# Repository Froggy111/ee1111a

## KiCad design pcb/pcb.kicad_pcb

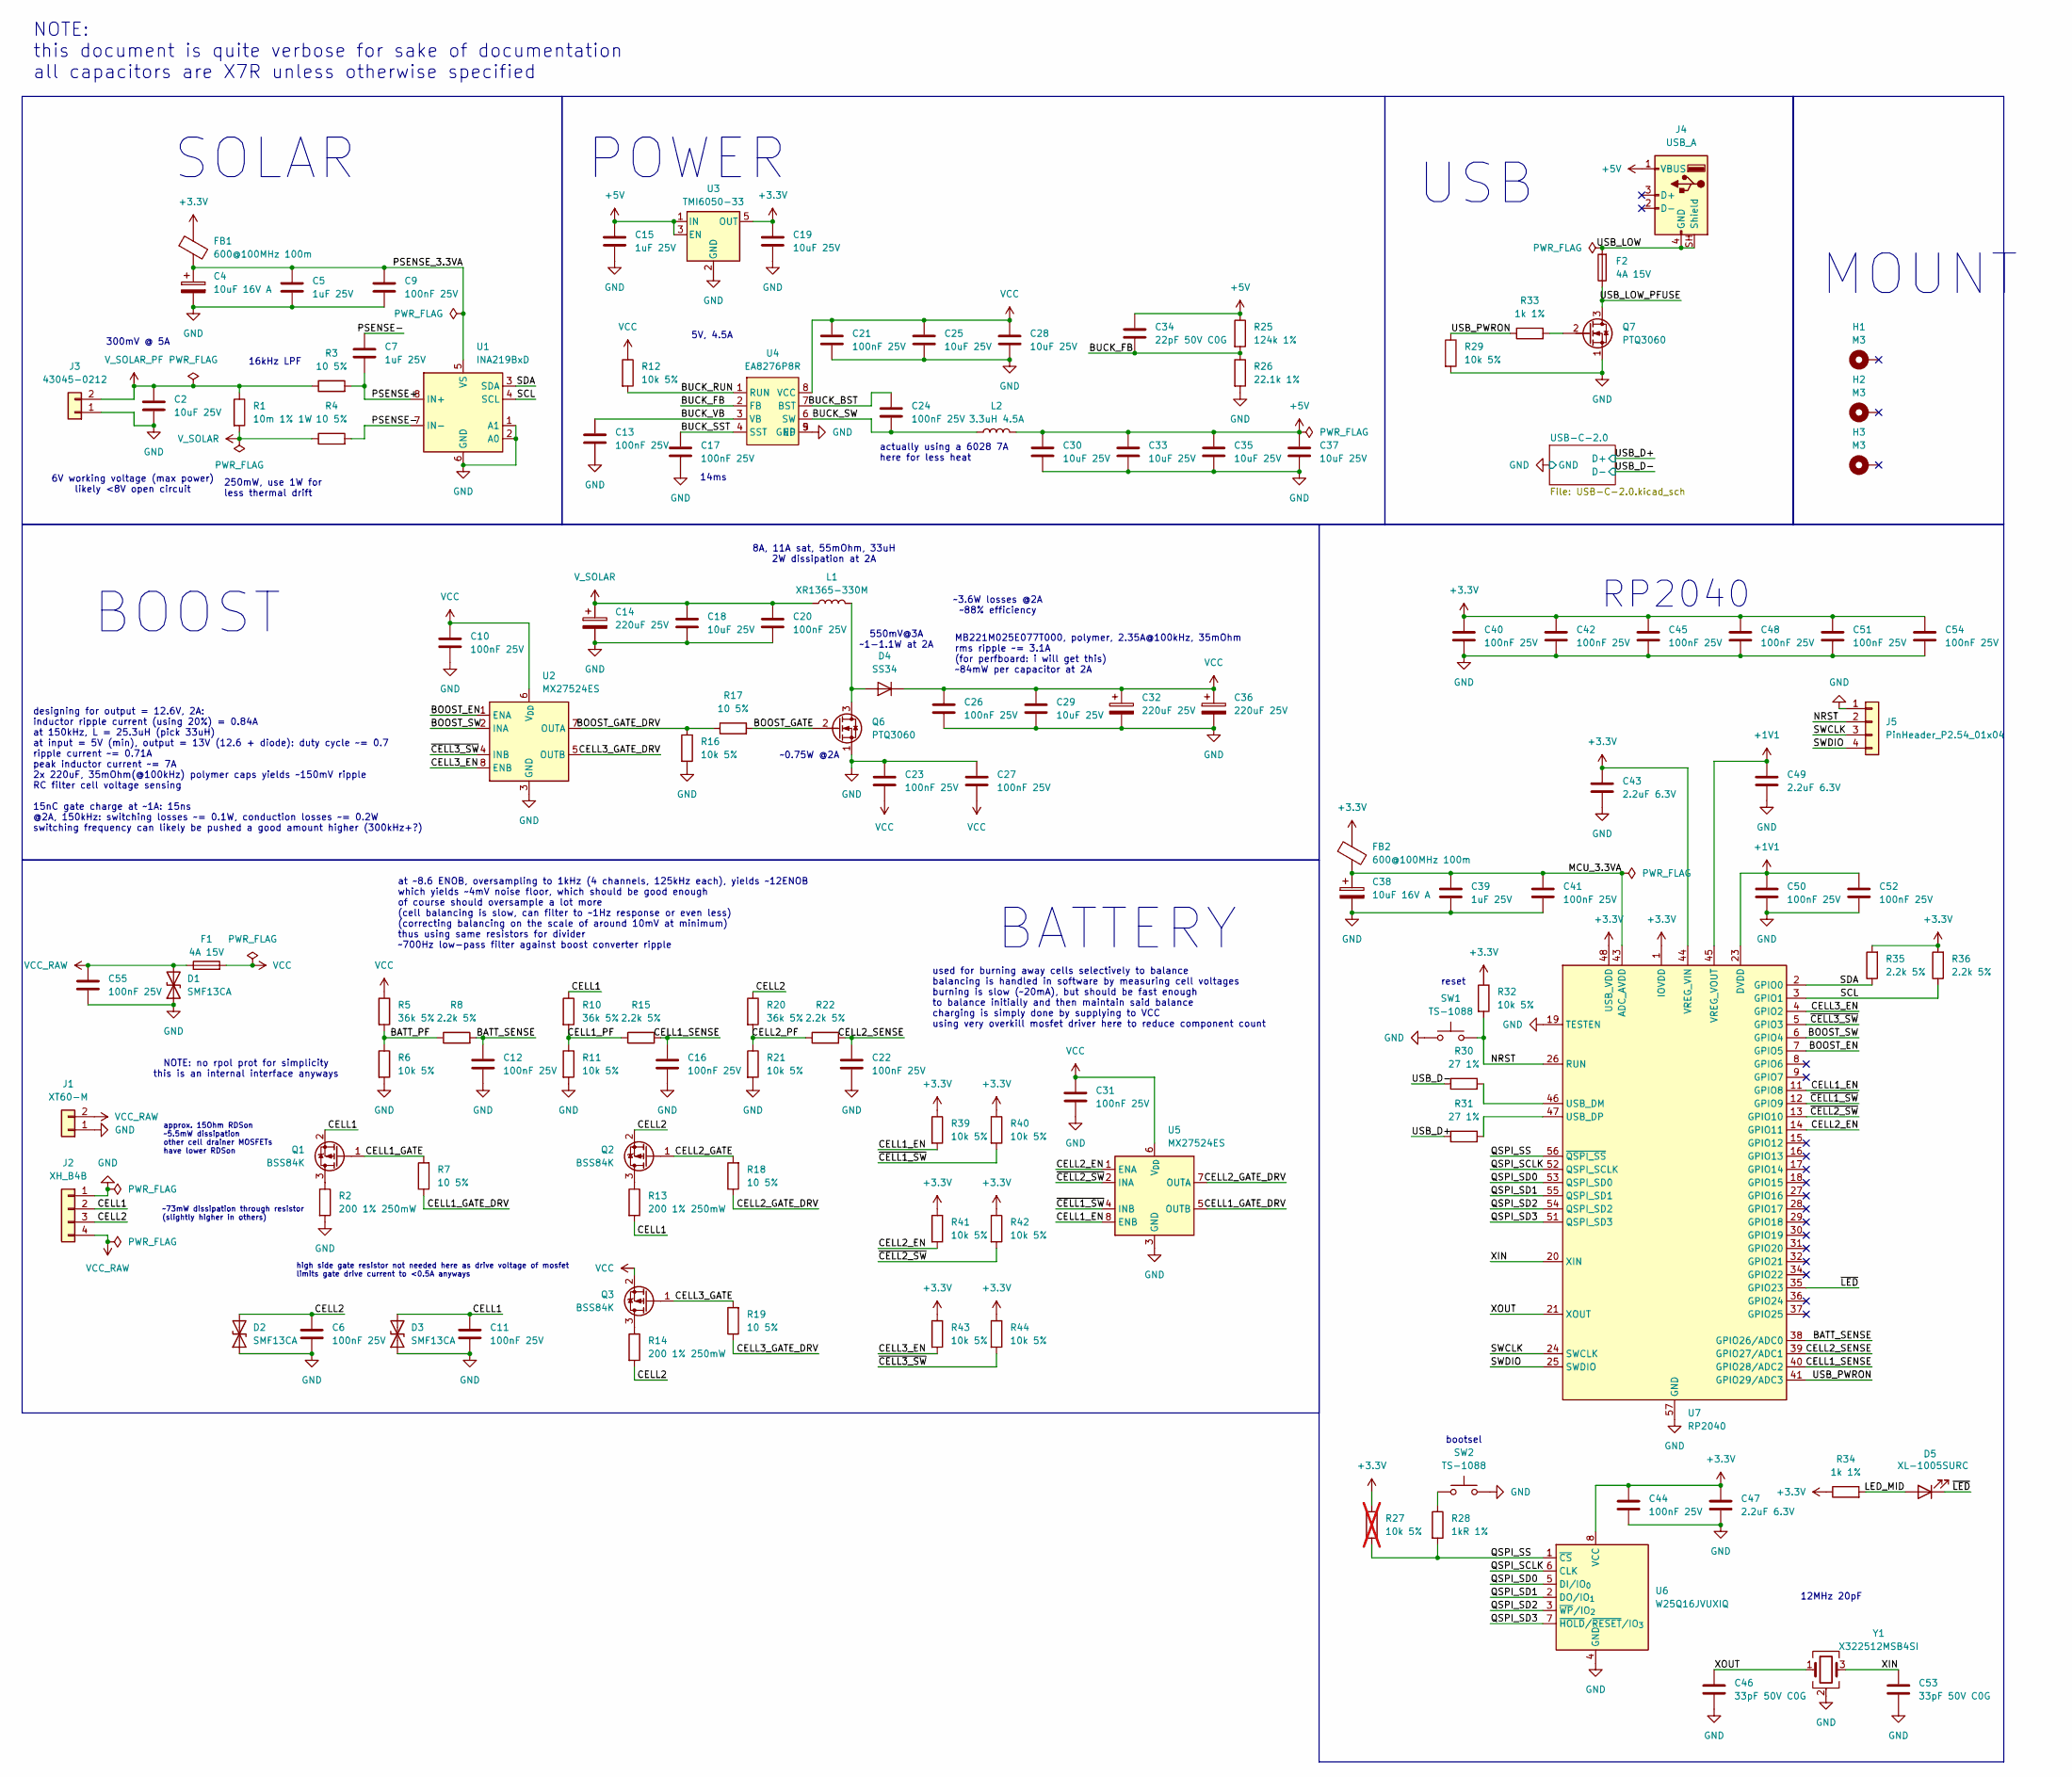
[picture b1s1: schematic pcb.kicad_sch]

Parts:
C2, C18, C19, C25, C28, C29, C30, C33, C35, C37: 10uF 25V; C_1206_3216Metric
C4, C38: 10uF 16V A; CP_EIA-3216-18_Kemet-A; MPN CA45-A016K106T
C5, C7, C15, C39: 1uF 25V; C_0603_1608Metric; MPN 0603B105M250NT
C6, C9, C10, C11, C12, C13, C16, C17, C20, C21, C22, C23, C24, C26, C27, C31, C40, C41, C42, C44, C45, C48, C50, C51, C52, C54, C55: 100nF 25V; C_0402_1005Metric; MPN 0402B104K250NT
C14, C32, C36: 220uF 25V; CP_Elec_6.3x7.7
C34: 22pF 50V C0G; C_0402_1005Metric; MPN 0402B104K250NT
C43, C47, C49: 2.2uF 6.3V; C_0402_1005Metric; MPN 0402B104K250NT
C46, C53: 33pF 50V C0G; C_0402_1005Metric
D1, D2, D3: SMF13CA; D_SOD-123F
D4: SS34; D_SMA
D5: XL-1005SURC; LED_0402_1005Metric; MPN XL-1005SURC
F1, F2: 4A 15V; Fuse_1206_3216Metric; MPN BFS1206-4000T/S
FB1, FB2: 600@100MHz 100m; L_0805_2012Metric; MPN CBM201209U601T
H1, H2, H3: M3; MountingHole_3.2mm_M3_Pad_Via
J1: XT60-M; AMASS_XT60-M_1x02_P7.20mm_Vertical
J2: XH_B4B; JST_XH_B4B-XH-A_1x04_P2.50mm_Vertical
J3: 43045-0212; Molex_Micro-Fit_3.0_43045-0212_2x01_P3.00mm_Vertical
J4: USB_A; USB_A_Molex_67643_Horizontal
J5: PinHeader_P2.54_01x04; PinHeader_1x04_P2.54mm_Vertical
L1: XR1365-330M; IND-SMD_L13.5-W12.6
L2: 3.3uH 4.5A; L_Bourns-SRN6028
Q1, Q2, Q3: BSS84K; SOT-23
Q6, Q7: PTQ3060; PDFNWB-8L(3.3x3.3)
R1: 10m 1% 1W; R_1206_3216Metric
R2, R13, R14: 200 1% 250mW; R_1206_3216Metric; MPN 1206W4F2000T5E
R3, R4, R7, R17, R18, R19: 10 5%; R_0402_1005Metric
R5, R10, R20: 36k 5%; R_0402_1005Metric
R6, R11, R12, R16, R21, R29, R32, R39, R40, R41, R42, R43, R44: 10k 5%; R_0402_1005Metric
R8, R15, R22, R35, R36: 2.2k 5%; R_0402_1005Metric
R25: 124k 1%; R_0402_1005Metric
R26: 22.1k 1%; R_0402_1005Metric
R27: 10k 5%; R_0402_1005Metric; not fitted
R28: 1kR 1%; R_0402_1005Metric
R30, R31: 27 1%; R_0402_1005Metric
R33, R34: 1k 1%; R_0402_1005Metric
SW1, SW2: TS-1088; SW_SPST_TS-1088-xR020; MPN TS-1088-AR02016
U1: INA219BxD; SOIC-8_3.9x4.9mm_P1.27mm
U2, U5: MX27524ES; Texas_DGN0008G_VSSOP-8-1EP_3x3mm_P0.65mm_EP2x2.94mm_Mask1.8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
U3: TMI6050-33; SOT-23-5
U4: EA8276P8R; HTSOP-8-1EP_3.9x4.9mm_P1.27mm_EP2.4x3.2mm_ThermalVias
U6: W25Q16JVUXIQ; Winbond_USON-8-1EP_3x2mm_P0.5mm_EP0.2x1.6mm
U7: RP2040; QFN-56-1EP_7x7mm_P0.4mm_EP3.2x3.2mm
Y1: X322512MSB4SI; Crystal_SMD_3225-4Pin_3.2x2.5mm

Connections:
+1V1: C49.1, C50.1, C52.1, U7.23 (DVDD), U7.45 (VREG_VOUT), U7.50 (DVDD)
+3.3V: C19.1, C40.1, C42.1, C43.1, C44.1, C45.1, C47.1, C48.1, C51.1, C54.1, FB1.1, FB2.1, R27.1, R32.1, R34.1, R35.2, R36.2, R39.1, R40.1, R41.1, R42.1, R43.1, R44.1, U3.5 (OUT), U6.8 (VCC), U7.1 (IOVDD), U7.10 (IOVDD), U7.22 (IOVDD), U7.33 (IOVDD), U7.42 (IOVDD), U7.44 (VREG_VIN), U7.48 (USB_VDD), U7.49 (IOVDD)
+5V: C15.1, C30.1, C33.1, C34.1, C35.1, C37.1, J4.1 (VBUS), L2.2, R25.1, U3.1 (IN), U3.3 (EN)
/BATT_PF: R5.2, R6.1, R8.1
/BATT_SENSE: C12.1, R8.2, U7.38 (GPIO26/ADC0)
/BOOST_EN: U2.1 (ENA), U7.7 (GPIO5)
/BOOST_GATE: Q6.2 (G), R17.2
/BOOST_GATE_DRV: R16.1, R17.1, U2.7 (OUTA)
/BOOST_SW: U2.2 (INA), U7.6 (GPIO4)
/BUCK_BST: C24.1, U4.7 (BST)
/BUCK_FB: C34.2, R25.2, R26.1, U4.2 (FB)
/BUCK_RUN: R12.2, U4.1 (RUN)
/BUCK_SST: C17.1, U4.4 (SST)
/BUCK_SW: C24.2, L2.1, U4.6 (SW)
/BUCK_VB: C13.1, U4.3 (VB)
/CELL1: C11.1, D3.2 (A2), J2.2, Q1.2 (S), R10.1, R13.2
/CELL1_EN: R39.2, U5.8 (ENB), U7.11 (GPIO8)
/CELL1_GATE: Q1.1 (G), R7.2
/CELL1_GATE_DRV: R7.1, U5.5 (OUTB)
/CELL1_PF: R10.2, R11.1, R15.1
/CELL1_SENSE: C16.1, R15.2, U7.40 (GPIO28/ADC2)
/CELL2: C6.1, D2.2 (A2), J2.3, Q2.2 (S), R14.2, R20.1
/CELL2_EN: R41.2, U5.1 (ENA), U7.14 (GPIO11)
/CELL2_GATE: Q2.1 (G), R18.2
/CELL2_GATE_DRV: R18.1, U5.7 (OUTA)
/CELL2_PF: R20.2, R21.1, R22.1
/CELL2_SENSE: C22.1, R22.2, U7.39 (GPIO27/ADC1)
/CELL3_EN: R43.2, U2.8 (ENB), U7.4 (GPIO2)
/CELL3_GATE: Q3.1 (G), R19.2
/CELL3_GATE_DRV: R19.1, U2.5 (OUTB)
/LED_MID: D5.2 (A), R34.2
/MCU_3.3VA: C38.1, C39.1, C41.1, FB2.2, U7.43 (ADC_AVDD)
/NRST: J5.2, R32.2, SW1.2, U7.26 (RUN)
/PSENSE+: C7.2, R3.2, U1.8 (IN+)
/PSENSE-: C7.1, R4.2, U1.7 (IN-)
/PSENSE_3.3VA: C4.1, C5.1, C9.1, FB1.2, U1.5 (VS)
/QSPI_SCLK: U6.6 (CLK), U7.52 (QSPI_SCLK)
/QSPI_SD0: U6.5 (DI/IO_{0}), U7.53 (QSPI_SD0)
/QSPI_SD1: U6.2 (DO/IO_{1}), U7.55 (QSPI_SD1)
/QSPI_SD2: U6.3 (~WP/IO_{2}), U7.54 (QSPI_SD2)
/QSPI_SD3: U6.7 (~HOLD/~RESET/IO_{3}), U7.51 (QSPI_SD3)
/QSPI_SS: R27.2, R28.2, U6.1 (~CS), U7.56 (~QSPI_SS)
/SCL: R36.1, U1.4 (SCL), U7.3 (GPIO1)
/SDA: R35.1, U1.3 (SDA), U7.2 (GPIO0)
/SWCLK: J5.3, U7.24 (SWCLK)
/SWDIO: J5.4, U7.25 (SWDIO)
/USB_D+: R31.1; also elsewhere on the board
/USB_D-: R30.1; also elsewhere on the board
/USB_LOW: F2.2, J4.4 (GND), J4.SH (Shield)
/USB_LOW_PFUSE: F2.1, Q7.3 (D)
/USB_PWRON: R29.1, R33.1, U7.41 (GPIO29/ADC3)
/XIN: C53.1, U7.20 (XIN), Y1.3
/XOUT: C46.1, U7.21 (XOUT), Y1.1
/~CELL1_SW: R40.2, U5.4 (INB), U7.12 (GPIO9)
/~CELL2_SW: R42.2, U5.2 (INA), U7.13 (GPIO10)
/~CELL3_SW: R44.2, U2.4 (INB), U7.5 (GPIO3)
/~LED: D5.1 (K), U7.35 (GPIO23)
GND: C2.2, C4.2, C5.2, C6.2, C9.2, C10.2, C11.2, C12.2, C13.2, C14.2, C15.2, C16.2, C17.2, C18.2, C19.2, C20.2, C21.2, C22.2, C23.1, C25.2, C26.2, C27.1, C28.2, C29.2, C30.2, C31.2, C32.2, C33.2, C35.2, C36.2, C37.2, C38.2, C39.2, C40.2, C41.2, C42.2, C43.2, C44.2, C45.2, C46.2, C47.2, C48.2, C49.2, C50.2, C51.2, C52.2, C53.2, C54.2, C55.2, D1.1 (A1), D2.1 (A1), D3.1 (A1), J1.1, J2.1, J3.1, J5.1, Q6.1 (S), Q7.1 (S), R2.2, R6.2, R11.2, R16.2, R21.2, R26.2, R29.2, SW1.1, SW2.2, U1.1 (A1), U1.2 (A0), U1.6 (GND), U2.3 (GND), U2.9 (GND), U3.2 (GND), U4.5 (GND), U4.9 (EP), U5.3 (GND), U5.9 (GND), U6.4 (GND), U6.9 (EP), U7.19 (TESTEN), U7.57 (GND), Y1.2 (G), Y1.4 (G); also elsewhere on the board
unnamed: D4.2 (A), L1.2, Q6.3 (D)
unnamed: Q1.3 (D), R2.1
unnamed: Q2.3 (D), R13.1
unnamed: Q3.3 (D), R14.1
unnamed: Q7.2 (G), R33.2
unnamed: R28.1, SW2.1
unnamed: R30.2, U7.46 (USB_DM)
unnamed: R31.2, U7.47 (USB_DP)
VCC: C10.1, C21.1, C23.2, C25.1, C26.1, C27.2, C28.1, C29.1, C31.1, C32.1, C36.1, D4.1 (K), F1.2, Q3.2 (S), R5.1, R12.1, U2.6 (V_{DD}), U4.8 (VCC), U5.6 (V_{DD})
VCC_RAW: C55.1, D1.2 (A2), F1.1, J1.2, J2.4
V_SOLAR: C14.1, C18.1, C20.1, L1.1, R1.2, R4.1
V_SOLAR_PF: C2.1, J3.2, R1.1, R3.1

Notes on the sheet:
actually using a 6028 7A here for less heat
~73mW dissipation through resistor (slightly higher in others)
POWER
300mV @ 5A
designing for output = 12.6V, 2A: inductor ripple current (using 20%) = 0.84A at 150kHz, L = 25.3uH (pick 33uH) at input = 5V (min), output = 13V (12.6 + diode): duty cycle ~= 0.7 ripple current ~= 0.71A peak inductor current ~= 7A 2x 220uF, 35mOhm(@100kHz) polymer caps yields ~150mV ripple RC filt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
NOTE: this document is quite verbose for sake of documentation all capacitors are X7R unless otherwise specified
SOLAR
14ms
~3.6W losses @2A ~88% efficiency
12MHz 20pF
NOTE: no rpol prot for simplicity this is an internal interface anyways
at ~8.6 ENOB, oversampling to 1kHz (4 channels, 125kHz each), yields ~12ENOB which yields ~4mV noise floor, which should be good enough of course should oversample a lot more (cell balancing is slow, can filter to ~1Hz response or even less) (correcting balancing on the scale of around 10mV at mini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
~0.75W @2A
16kHz LPF
250mW, use 1W for less thermal drift
RP2040
MOUNT
550mV@3A ~1-1.1W at 2A
6V working voltage (max power) likely <8V open circuit
8A, 11A sat, 55mOhm, 33uH 2W dissipation at 2A
BOOST
MB221M025E077T000, polymer, 2.35A@100kHz, 35mOhm rms ripple ~= 3.1A (for perfboard: i will get this) ~84mW per capacitor at 2A
5V, 4.5A
reset
approx. 15Ohm RDSon ~5.5mW dissipation other cell drainer MOSFETs have lower RDSon
high side gate resistor not needed here as drive voltage of mosfet limits gate drive current to <0.5A anyways
bootsel
BATTERY
USB
used for burning away cells selectively to balance balancing is handled in software by measuring cell voltages burning is slow (~20mA), but should be fast enough to balance initially and then maintain said balance charging is simply done by supplying to VCC using very overkill mosfet driver here to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

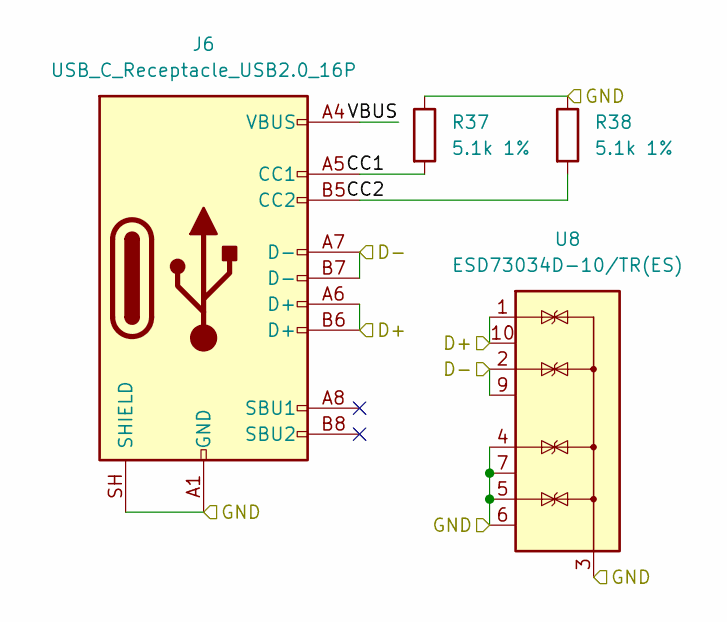
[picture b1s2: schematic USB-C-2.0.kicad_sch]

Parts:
J6: USB_C_Receptacle_USB2.0_16P; USB_C_Receptacle_16P; MPN TYPE-C 16PIN 2MD(073)
R37, R38: 5.1k 1%; R_0402_1005Metric; MPN RC-02K512JT
U8: ESD73034D-10/TR(ES); Diodes_UDFN-10_1x2.5mm_P0.5mm; MPN ESD73034D-10/TR(ES)

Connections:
/USB-C-2.0/CC1: J6.A5 (CC1), R37.2
/USB-C-2.0/CC2: J6.B5 (CC2), R38.2
/USB-C-2.0/VBUS: J6.A4 (VBUS), J6.A9 (VBUS), J6.B4 (VBUS), J6.B9 (VBUS)
/USB_D+: J6.A6 (D+), J6.B6 (D+), U8.1 (IO1), U8.10 (NC); also elsewhere on the board
/USB_D-: J6.A7 (D-), J6.B7 (D-), U8.2 (IO2), U8.9 (NC); also elsewhere on the board
GND: J6.A1 (GND), J6.A12 (GND), J6.B1 (GND), J6.B12 (GND), J6.SH (SHIELD), R37.1, R38.1, U8.3 (G), U8.4 (IO3), U8.5 (IO4), U8.6 (NC), U8.7 (NC), U8.8 (G); also elsewhere on the board

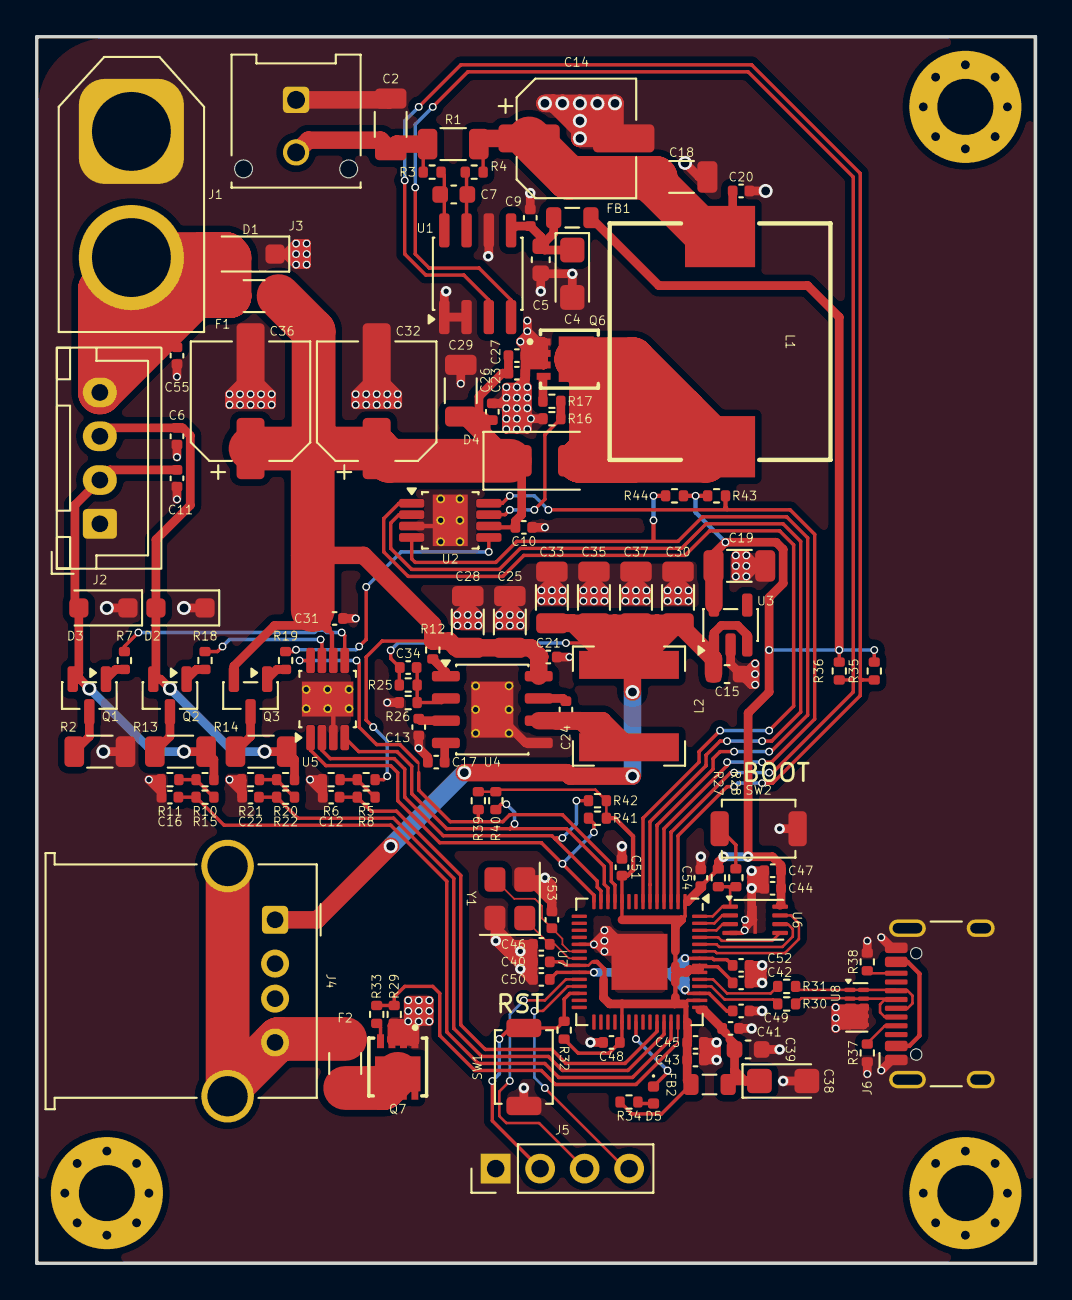
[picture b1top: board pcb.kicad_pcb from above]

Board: 2 copper layers, 57.0 x 70.0 mm, 129 parts (0 on the bottom side), 73 nets.

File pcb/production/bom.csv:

Designator,Footprint,Quantity,Value,LCSC Part #
"C10, C11, C12, C13, C16, C17, C20, C21, C22, C23, C24, C26, C27, C31, C40, C41, C42, C44, C45, C48, C50, C51, C52, C54, C55, C6, C9",0402,27,100nF 25V,0402B104K250NT
"C14, C32, C36",CP_Elec_6.3x7.7,3,220uF 25V,
"C15, C39, C5, C7",0603,4,1uF 25V,0603B105M250NT
"C18, C19, C2, C25, C28, C29, C30, C33, C35, C37",1206,10,10uF 25V,
C34,0402,1,22pF 50V C0G,0402B104K250NT
"C38, C4",CP_EIA-3216-18_Kemet-A,2,10uF 16V A,CA45-A016K106T
"C43, C47, C49",0402,3,2.2uF 6.3V,0402B104K250NT
"C46, C53",0402,2,33pF 50V C0G,
"D1, D2, D3",D_SOD-123F,3,SMF13CA,
D4,D_SMA,1,SS34,
D5,0402,1,XL-1005SURC,XL-1005SURC
"F1, F2",1206,2,4A 15V,BFS1206-4000T/S
"FB1, FB2",0805,2,600@100MHz 100m,CBM201209U601T
J1,AMASS_XT60-M_1x02_P7.20mm_Vertical,1,XT60-M,
J2,JST_XH_B4B-XH-A_1x04_P2.50mm_Vertical,1,XH_B4B,
J3,Molex_Micro-Fit_3.0_43045-0212_2x01_P3.00mm_Vertical,1,43045-0212,
J4,USB_A_Molex_67643_Horizontal,1,USB_A,
J5,PinHeader_1x04_P2.54mm_Vertical,1,PinHeader_P2.54_01x04,
J6,USB_C_Receptacle_16P,1,USB_C_Receptacle_USB2.0_16P,TYPE-C 16PIN 2MD(073)
L1,IND-SMD_L13.5-W12.6,1,XR1365-330M,
L2,L_Bourns-SRN6028,1,3.3uH 4.5A,
"Q1, Q2, Q3",SOT-23,3,BSS84K,
"Q6, Q7",PDFNWB-8L(3.3x3.3),2,PTQ3060,
R1,1206,1,10m 1% 1W,
"R10, R20, R5",0402,3,36k 5%,
"R11, R12, R16, R21, R27, R29, R32, R39, R40, R41, R42, R43, R44, R6",0402,14,10k 5%,
"R13, R14, R2",1206,3,200 1% 250mW,1206W4F2000T5E
"R15, R22, R35, R36, R8",0402,5,2.2k 5%,
"R17, R18, R19, R3, R4, R7",0402,6,10 5%,
R25,0402,1,124k 1%,
R26,0402,1,22.1k 1%,
R28,0402,1,1kR 1%,
"R30, R31",0402,2,27 1%,
"R33, R34",0402,2,1k 1%,
"R37, R38",0402,2,5.1k 1%,RC-02K512JT
"SW1, SW2",SW_SPST_TS-1088-xR020,2,TS-1088,TS-1088-AR02016
U1,SOIC-8_3.9x4.9mm_P1.27mm,1,INA219BxD,
"U2, U5",Texas_DGN0008G_VSSOP-8-1EP_3x3mm_P0.65mm_EP2x2.94mm_Mask1.846x2.15mm_ThermalVias,2,MX27524ES,
U3,SOT-23-5,1,TMI6050-33,
U4,HTSOP-8-1EP_3.9x4.9mm_P1.27mm_EP2.4x3.2mm_ThermalVias,1,EA8276P8R,
U6,Winbond_USON-8-1EP_3x2mm_P0.5mm_EP0.2x1.6mm,1,W25Q16JVUXIQ,
U7,QFN-56-1EP_7x7mm_P0.4mm_EP3.2x3.2mm,1,RP2040,
U8,Diodes_UDFN-10_1x2.5mm_P0.5mm,1,ESD73034D-10/TR(ES),ESD73034D-10/TR(ES)
Y1,Crystal_SMD_3225-4Pin_3.2x2.5mm,1,X322512MSB4SI,

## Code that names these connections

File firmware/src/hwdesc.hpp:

#include <hardware/i2c.h>

#include "types.hpp"
using namespace types;

namespace hwdesc {

const u8 I2C_INST = 0;
const u8 CELL1_ADC_CH = 2;
const u8 CELL2_ADC_CH = 1;
const u8 BATT_ADC_CH = 0;
const float VSENSE_SCALE = ((10.0 + 36.0) / 10.0) * (3.3 / (1 << 12));

const u8 INA219B_ADDR = 0b1000000;

namespace pins {
const u8 SDA = 0;
const u8 SCL = 1;
const u8 NLED = 23;
const u8 USB_PWRON = 29;

const u8 CELL1_SENSE = 28;
const u8 CELL2_SENSE = 27;
const u8 BATT_SENSE = 26;

const u8 BOOST_EN = 5;
/// 2A
const u8 BOOST_SW = 4;

namespace drain {
const u8 EN1 = 8;
/// 4B
const u8 NSW1 = 9;
const u8 EN2 = 11;
/// 5A
const u8 NSW2 = 10;
const u8 EN3 = 2;
/// 1B
const u8 NSW3 = 3;
}  // namespace drain
}  // namespace pins

}  // namespace hwdesc
